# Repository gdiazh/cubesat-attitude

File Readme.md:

Proyecto: Attitude Control for cubesat
--------------------------------------

[TOC]

# Resumen

El proyecto se realiza para el curso EL5004-Taller de Diseño. Más detalles en la wiki.

# Recursos

## Hardware

TO DO

## Software

TO DO

# Contenido del proyecto

TO DO

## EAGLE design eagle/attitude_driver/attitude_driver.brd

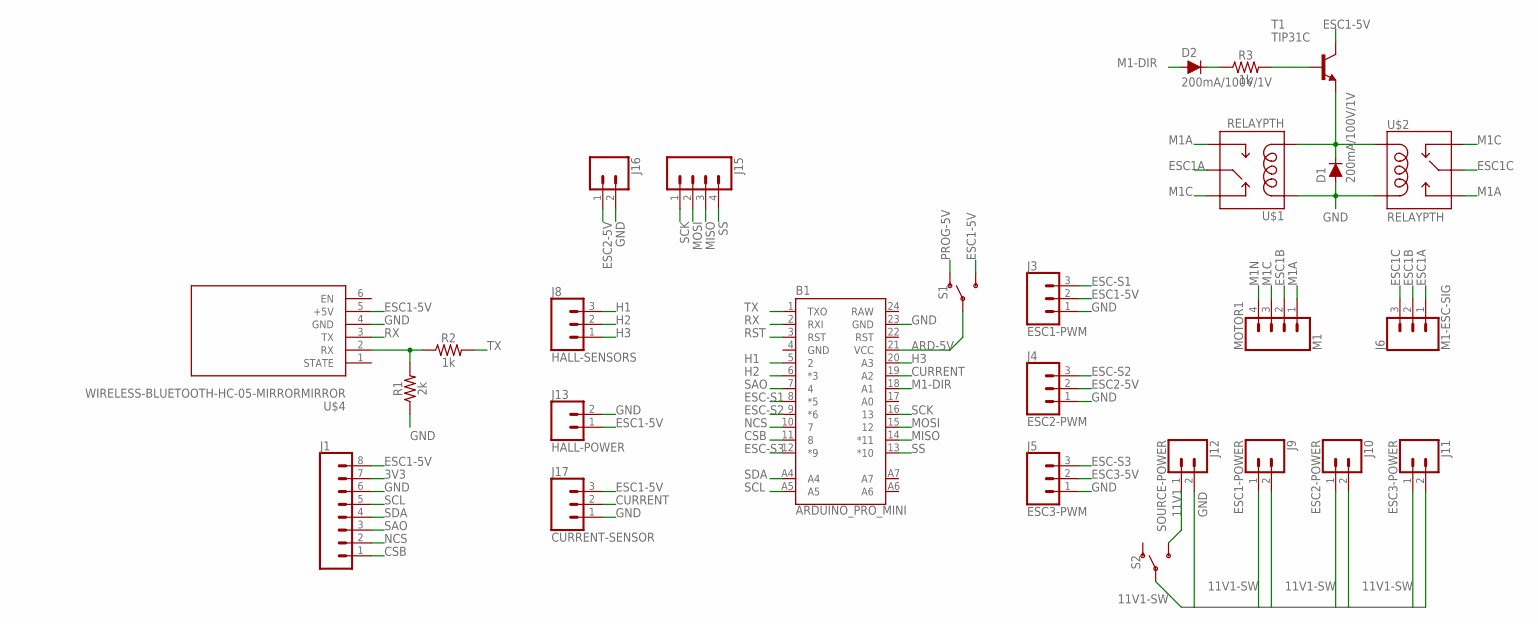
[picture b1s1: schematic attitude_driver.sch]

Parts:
B1: ARDUINO_PRO_MINI
D1, D2: 200mA/100V/1V; DIODE-1N4148
J1: GY-91LOCK_LONGPADS; GY91_LONGPADS
J3: ESC1-PWM; 1X03_LOCK_LONGPADS
J4: ESC2-PWM; 1X03_LOCK_LONGPADS
J5: ESC3-PWM; 1X03_LOCK_LONGPADS
J6: M1-ESC-SIG; 1X03_LOCK_LONGPADS
J8: HALL-SENSORS; 1X03_LOCK_LONGPADS
J9: ESC1-POWER; 1X02_LOCK_LONGPADS
J10: ESC2-POWER; 1X02_LOCK_LONGPADS
J11: ESC3-POWER; 1X02_LOCK_LONGPADS
J12: SOURCE-POWER; 1X02_LOCK_LONGPADS
J13: HALL-POWER; 1X02_LOCK_LONGPADS
J15: CONN_04LOCK_LONGPADS; 1X04_LOCK_LONGPADS
J16: CONN_02LOCK_LONGPADS; 1X02_LOCK_LONGPADS
J17: CURRENT-SENSOR; 1X03_LOCK_LONGPADS
MOTOR1: M1; 1X04_LOCK_LONGPADS
R1: 2k; AXIAL-0.3
R2, R3: 1k; AXIAL-0.3
S1, S2: SWITCH-SPDT-PTH-11.6X4.0MM-LOCK; SWITCH_SPDT_PTH_11.6X4.0MM_LOCK
T1: TIP31C; TO220
U$1, U$2: RELAYPTH; SRD-05VDC-SL-C
U$4: WIRELESS-BLUETOOTH-HC-05-MIRRORMIRROR; WIRELESS-BLUETOOTH-HC-05-MIRROR

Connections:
3V3: J1.7
11V1: J12.1, S2.3 (S)
11V1-SW: J9.1, J10.1, J11.1, S2.2
ARD-5V: B1.21 (VCC), S1.2
CSB: B1.11 (8), J1.1
CURRENT: B1.19 (A2), J17.2
ESC1-5V: J1.8, J3.2, J13.1, J17.3, S1.3 (S), T1.2 (C), U$4.5 (+5V)
ESC1A: J6.1, U$1.SWCOMMON
ESC1B: J6.2, MOTOR1.2
ESC1C: J6.3, U$2.SWCOMMON
ESC2-5V: J4.2, J16.1
ESC3-5V: J5.2
ESC-S1: B1.8 (*5), J3.3
ESC-S2: B1.9 (*6), J4.3
ESC-S3: B1.12 (*9), J5.3
GND: B1.4 (GND), B1.23 (GND), D1.A, D1.C, J1.6, J3.1, J4.1, J5.1, J9.2, J10.2, J11.2, J12.2, J13.2, J16.2, J17.1, R1.P$1 (1), T1.3 (E), U$1.COIL0, U$1.COIL1, U$2.COIL0, U$2.COIL1, U$4.4 (GND)
H1: B1.5 (2), J8.3
H2: B1.6 (*3), J8.2
H3: B1.20 (A3), J8.1
M1-DIR: B1.18 (A1), D2.A
M1A: MOTOR1.1, U$1.SWOPEN, U$2.SWOPEN
M1C: MOTOR1.3, U$1.SWCLOSED (SWCLOSE), U$2.SWCLOSED (SWCLOSE)
M1N: MOTOR1.4
MISO: B1.14 (*11), J15.3
MOSI: B1.15 (12), J15.2
unnamed: R1.P$2 (2), R2.P$1 (1), U$4.2 (RX)
unnamed: R3.P$2 (2), T1.1 (B)
unnamed: D2.C, R3.P$1 (1)
NCS: B1.10 (7), J1.2
PROG-5V: S1.1 (O)
RAW: B1.24 (RAW)
RST: B1.3 (RST)
RX: B1.2 (RXI), U$4.3 (TX)
SAO: B1.7 (4), J1.3
SCK: B1.16 (13), J15.1
SCL: B1.A5, J1.5
SDA: B1.A4, J1.4
SS: B1.13 (*10), J15.4
TX: B1.1 (TXO), R2.P$2 (2)

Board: 2 copper layers, 27 parts (0 on the bottom side), 33 nets, no tracks yet.

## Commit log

2017-05-25 start tracking the project
2017-07-01 add bt-interface working
2017-07-02 Increase frame length, 4 floats sent ok
2017-07-02 PID test with pitch angle
2017-07-20 yaw angle controller using dmp example
2017-07-22 working with new shield
2017-07-23 add operation modes
2017-07-24 ros-interface tested OK
2017-07-31 tunning pid
2017-08-30 improve command interface
2017-09-17 add hall sensor and second motor, tested ok
2017-10-04 protocol ok, added speed filter
2017-10-05 added urdf and ros_package
2017-10-06 added some sdf properties
2017-10-07 added velocity controllers
2017-10-23 changes based on speed test
2017-10-23 eagle files
2017-10-23 ordered components
2017-11-09 working on promini uC
2017-11-15 added first current sensor
2017-11-16 changes for identification test
2017-11-17 voltage, pwm and rmp first calibration
2017-11-18 change driver structure
2017-11-18 update ros interface
2017-11-19 motor model
2017-11-19 estimation script
2017-11-20 mean values
2017-11-20 voltage open loop test ok
2017-11-20 km torque motor constant test
2017-11-21 add more mesurement for kt
2017-11-21 KM estimate with 10 measurements
2017-11-23 model vs data
2017-11-24 tested current controller
2017-11-24 air bearing and sat on gazebo
2017-11-24 tunning speed controller
2017-11-26 yaw model
2017-11-27 estimate KM based current and speed
2017-11-27 current control graph script
2017-11-27 tunnig speed controller
2017-11-29 tunning yaw controller
2017-12-01 still tunning yaw controller
2017-12-03 change yaw-angle domain
2017-12-05 added current controller for second motor
2017-12-06 tunning second motor current controller
2017-12-07 adding bi-directional current controller
2017-12-09 tunning yaw controller
2017-12-13 integrate motor_y to controller and change parameters
2017-12-15 tunnig yaw controller
2017-12-18 yaw-control oscillatory
2017-12-19 tunning controllers ...
2017-12-20 update arduino mega vertion
2018-01-02 updating mega ADK vertion
2018-01-07 some rotation plots and quat visualization
2018-01-11 some quaternion calculations
2018-01-12 update pcb design
2018-02-03 change setpoint signal
2018-03-29 plot scripts ...
2018-03-29 new tests

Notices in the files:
parts and their libraries:
SparkFun-Boards: Licensing: Creative Commons ShareAlike 4.0 International - https://creativecommons.org/licenses/by-sa/4.0
diy-modules: Released under the Creative Commons Attribution 4.0 International License: http://creativecommons.org/licenses/by/4.0
